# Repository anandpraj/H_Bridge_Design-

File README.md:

# H_Bridge_Design-
An H-bridge is a simple circuit that lets you control a DC motor to go backward or forward.  You normally use it with a microcontroller, such as an Arduino, to control motors.  When you can control two motors to go either forward or backward – you can build yourself a robot!

Here I have designed a simple H-Bridge motor speed control circuit using KiCAD. The circuit consists of 2 pair of mosfets, 2 pair of resistors, two opto-isolators which can protect the microcontroller from sudden voltage spikes.

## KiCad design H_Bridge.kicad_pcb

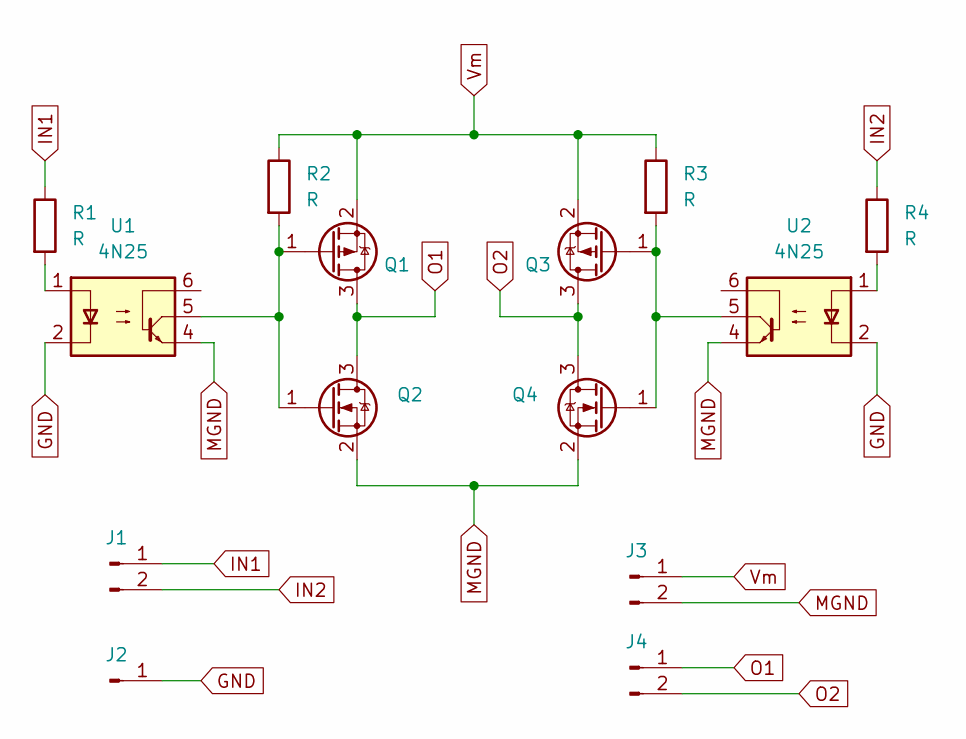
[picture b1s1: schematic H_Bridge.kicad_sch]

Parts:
J1, J3, J4: Conn_01x02_Male; PinHeader_1x02_P2.54mm_Vertical
J2: Conn_01x01_Male; PinHeader_1x01_P2.54mm_Vertical
Q1, Q3: AO3401A; SOT-23
Q2, Q4: IRLML0030; SOT-23
R1, R2, R3, R4: R; R_0805_2012Metric_Pad1.20x1.40mm_HandSolder
U1, U2: 4N25; DIP-6_W7.62mm

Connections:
GND: J2.1, U1.2, U2.2
IN1: J1.1, R1.1
IN2: J1.2, R4.1
MGND: J3.2, Q2.2 (S), Q4.2 (S), U1.4, U2.4
unnamed: Q1.1 (G), Q2.1 (G), R2.2, U1.5
unnamed: Q3.1 (G), Q4.1 (G), R3.2, U2.5
unnamed: R1.2, U1.1
unnamed: R4.2, U2.1
O1: J4.1, Q1.3 (D), Q2.3 (D)
O2: J4.2, Q3.3 (D), Q4.3 (D)
Vm: J3.1, Q1.2 (S), Q3.2 (S), R2.1, R3.1

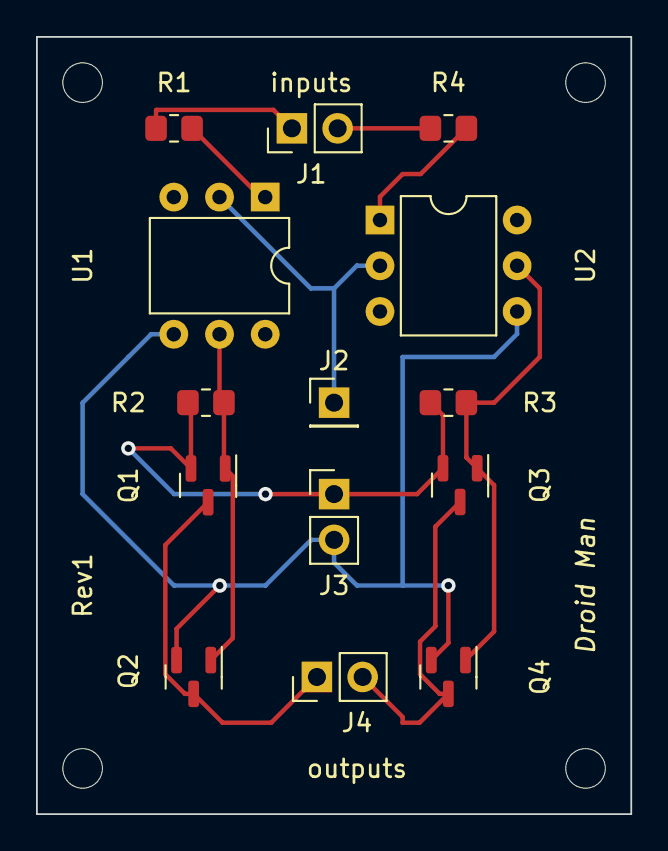
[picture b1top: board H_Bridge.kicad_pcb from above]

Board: 2 copper layers, 33.0 x 43.2 mm, 14 parts (0 on the bottom side), 11 nets.
